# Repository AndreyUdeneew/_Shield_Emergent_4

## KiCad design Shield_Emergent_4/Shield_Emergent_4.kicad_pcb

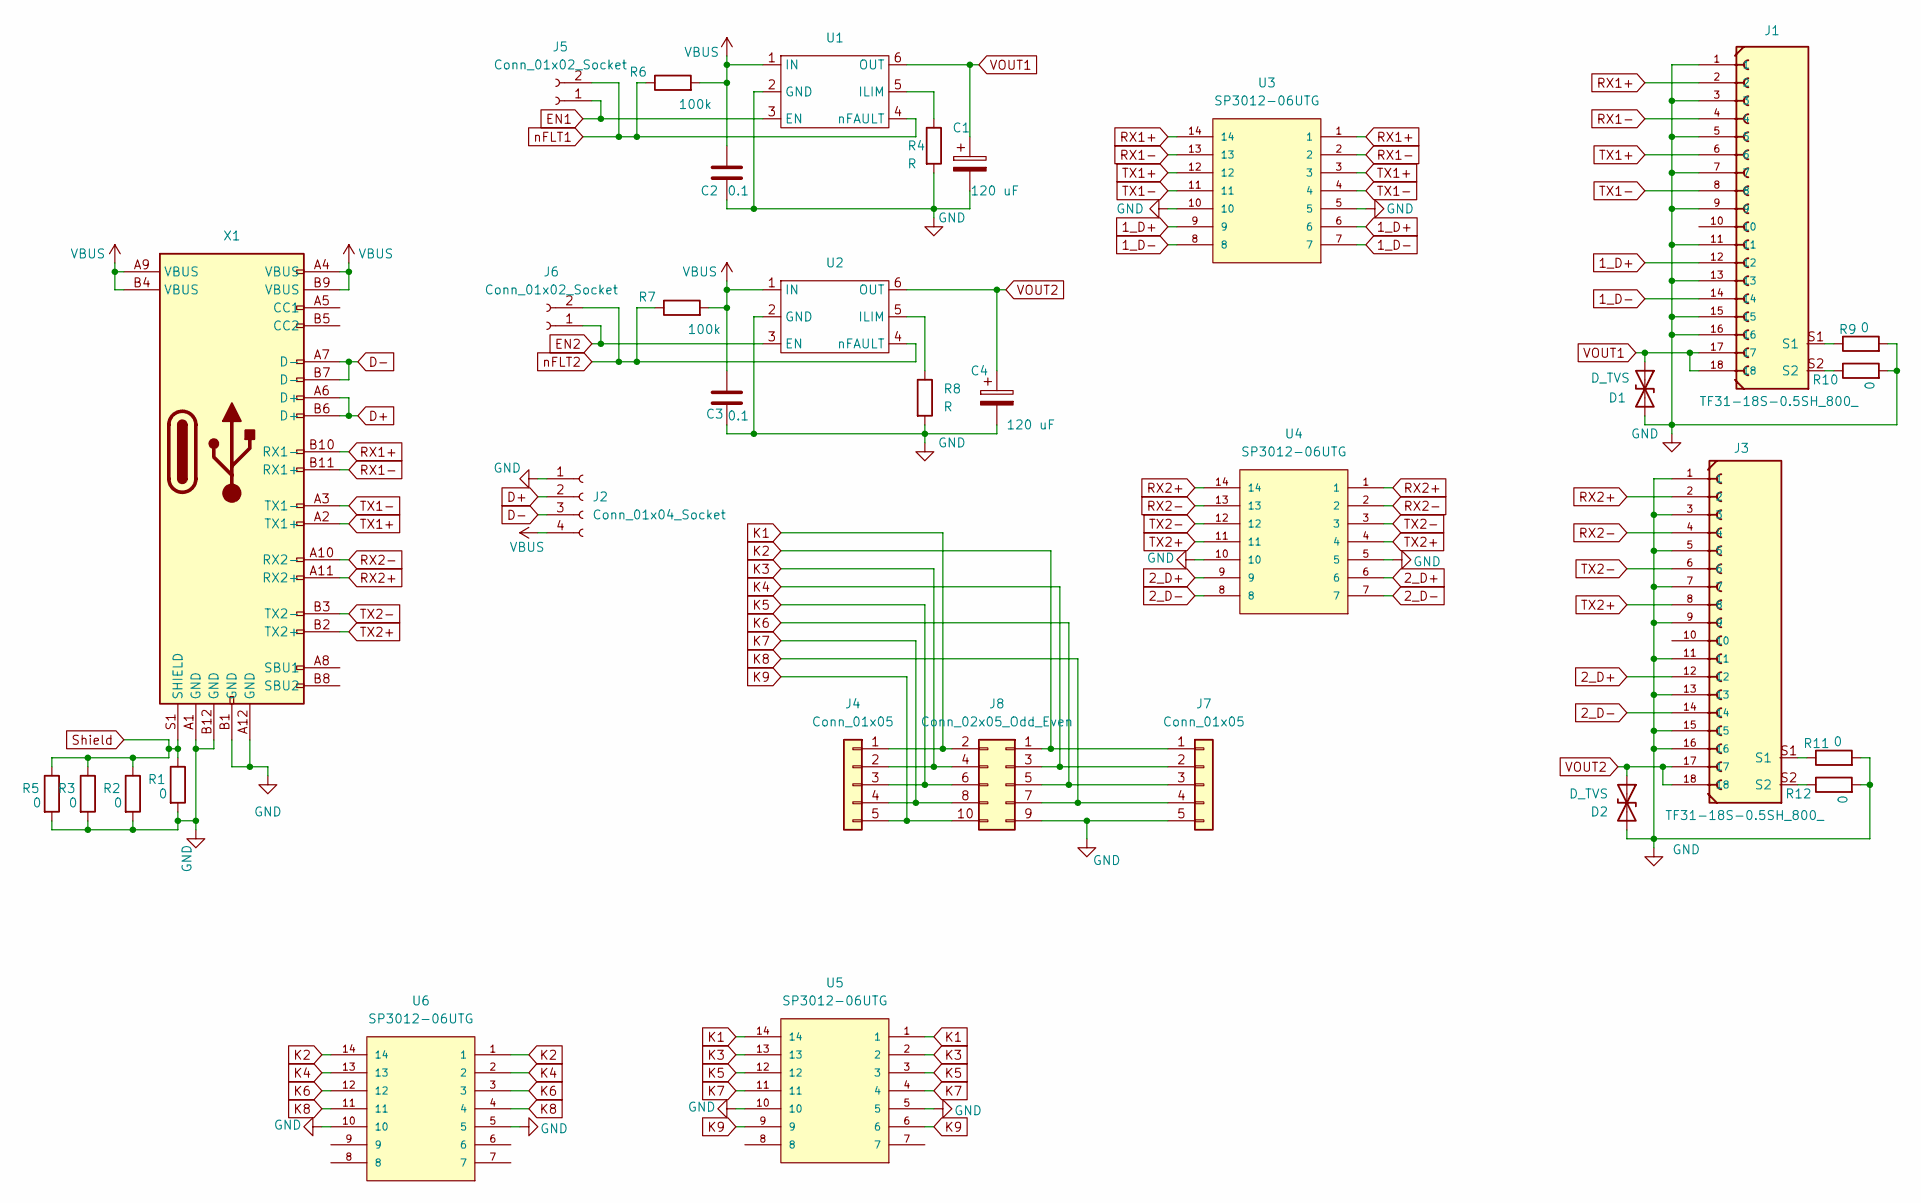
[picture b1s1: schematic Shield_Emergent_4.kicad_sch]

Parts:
C1, C4: 120 uF; CP_Elec_6.3x7.7
C2, C3: 0.1; C_0402_1005Metric_Pad0.74x0.62mm_HandSolder
D1, D2: D_TVS; D_SOD-523
J1, J3: TF31-18S-0.5SH_800_; HRS_TF31-18S-0.5SH_800_
J2: Conn_01x04_Socket; PinSocket_1x04_P2.54mm_Vertical
J4, J7: Conn_01x05; PinHeader_1x05_P1.27mm_Vertical
J5, J6: Conn_01x02_Socket; PinHeader_1x02_P1.27mm_Vertical
J8: Conn_02x05_Odd_Even; PinHeader_2x05_P1.27mm_Vertical
R1, R2, R3, R5, R9, R10, R11, R12: 0; R_0201_0603Metric_Pad0.64x0.40mm_HandSolder
R4, R8: R; R_0402_1005Metric_Pad0.72x0.64mm_HandSolder
R6, R7: 100k; R_0402_1005Metric_Pad0.72x0.64mm_HandSolder
U1, U2: SOT-23-6_Handsoldering
U3, U4, U5, U6: SP3012-06UTG; DFN-14_1.35x3.5mm_P0.5mm; PARTREV 02/23/17
X1: USB_C_24pins; USB_C_Receptacle_JAE_DX07S024WJ3R400

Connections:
1_D+: J1.12, U3.6, U3.9
1_D-: J1.14, U3.7, U3.8
2_D+: J3.12, U4.6, U4.9
2_D-: J3.14, U4.7, U4.8
D+: J2.2, X1.A6 (D+), X1.B6 (D+)
D-: J2.3, X1.A7 (D-), X1.B7 (D-)
EN1: J5.1, U1.3 (EN)
EN2: J6.1, U2.3 (EN)
GND: C1.2, C2.2, C3.2, C4.2, D1.2 (A2), D2.2 (A2), J1.1, J1.3, J1.5, J1.7, J1.9, J1.11, J1.13, J1.15, J1.16, J2.1, J3.1, J3.3, J3.5, J3.7, J3.9, J3.11, J3.13, J3.15, J3.16, J7.5, J8.9, R1.2, R2.2, R3.2, R4.2, R5.2, R8.2, R9.2, R10.2, R11.2, R12.2, U1.2 (GND), U2.2 (GND), U3.5, U3.10, U4.5, U4.10, U5.5, U5.10, U6.5, U6.10, X1.A1 (GND), X1.A12 (GND), X1.B1 (GND), X1.B12 (GND)
K1: J4.1, J8.2, U5.1, U5.14
K2: J7.1, J8.1, U6.1, U6.14
K3: J4.2, J8.4, U5.2, U5.13
K4: J7.2, J8.3, U6.2, U6.13
K5: J4.3, J8.6, U5.3, U5.12
K6: J7.3, J8.5, U6.3, U6.12
K7: J4.4, J8.8, U5.4, U5.11
K8: J7.4, J8.7, U6.4, U6.11
K9: J4.5, J8.10, U5.6, U5.9
unnamed: J1.S1, R9.1
unnamed: J1.S2, R10.1
unnamed: J3.S1, R11.1
unnamed: J3.S2, R12.1
unnamed: R4.1, U1.5 (ILIM)
unnamed: R8.1, U2.5 (ILIM)
RX1+: J1.2, U3.1, U3.14, X1.B10 (RX1-)
RX1-: J1.4, U3.2, U3.13, X1.B11 (RX1+)
RX2+: J3.2, U4.1, U4.14, X1.A11 (RX2+)
RX2-: J3.4, U4.2, U4.13, X1.A10 (RX2-)
Shield: R1.1, R2.1, R3.1, R5.1, X1.S1 (SHIELD), X1.S2 (SHIELD), X1.S3 (SHIELD), X1.S4 (SHIELD)
TX1+: J1.6, U3.3, U3.12, X1.A2 (TX1+)
TX1-: J1.8, U3.4, U3.11, X1.A3 (TX1-)
TX2+: J3.8, U4.4, U4.11, X1.B2 (TX2+)
TX2-: J3.6, U4.3, U4.12, X1.B3 (TX2-)
VBUS: C2.1, C3.1, J2.4, R6.2, R7.2, U1.1 (IN), U2.1 (IN), X1.A4 (VBUS), X1.A9 (VBUS), X1.B4 (VBUS), X1.B9 (VBUS)
VOUT1: C1.1, D1.1 (A1), J1.17, J1.18, U1.6 (OUT)
VOUT2: C4.1, D2.1 (A1), J3.17, J3.18, U2.6 (OUT)
nFLT1: J5.2, R6.1, U1.4 (nFAULT)
nFLT2: J6.2, R7.1, U2.4 (nFAULT)

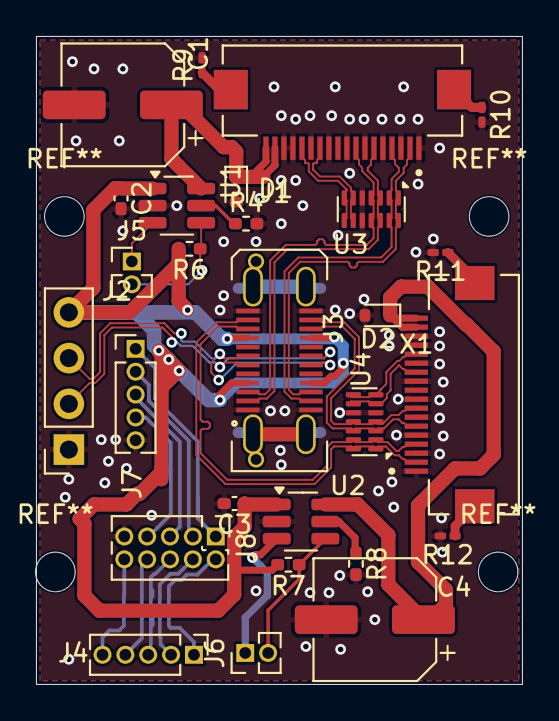
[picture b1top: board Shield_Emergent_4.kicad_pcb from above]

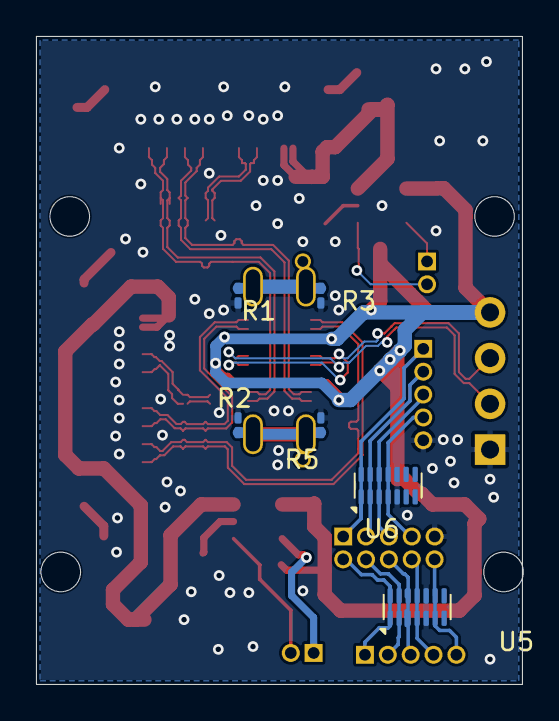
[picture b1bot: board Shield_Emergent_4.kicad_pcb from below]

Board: 4 copper layers, 27.0 x 36.0 mm, 33 parts (6 on the bottom side), 38 nets.

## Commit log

2024-08-16 v0.1 old diffpairs style
2024-08-16 v0.1 Modification with diffpairs 0.112 x 0.127 mm
2024-08-16 v0.3 LF circuits were routed
2024-08-19 v0.4 Seems 2B ready
2024-08-19 v0.5 modified and ordered
2024-10-07 v0.6 new geometry
2024-10-08 v0.7 predecomposition was completed
2024-10-09 м0,8 reflection was committed
2024-10-28 v0.9 draft routing was completed
2024-10-28 v0.91 changes were saved
2024-10-28 v1.0 diffpairs routed correctly
